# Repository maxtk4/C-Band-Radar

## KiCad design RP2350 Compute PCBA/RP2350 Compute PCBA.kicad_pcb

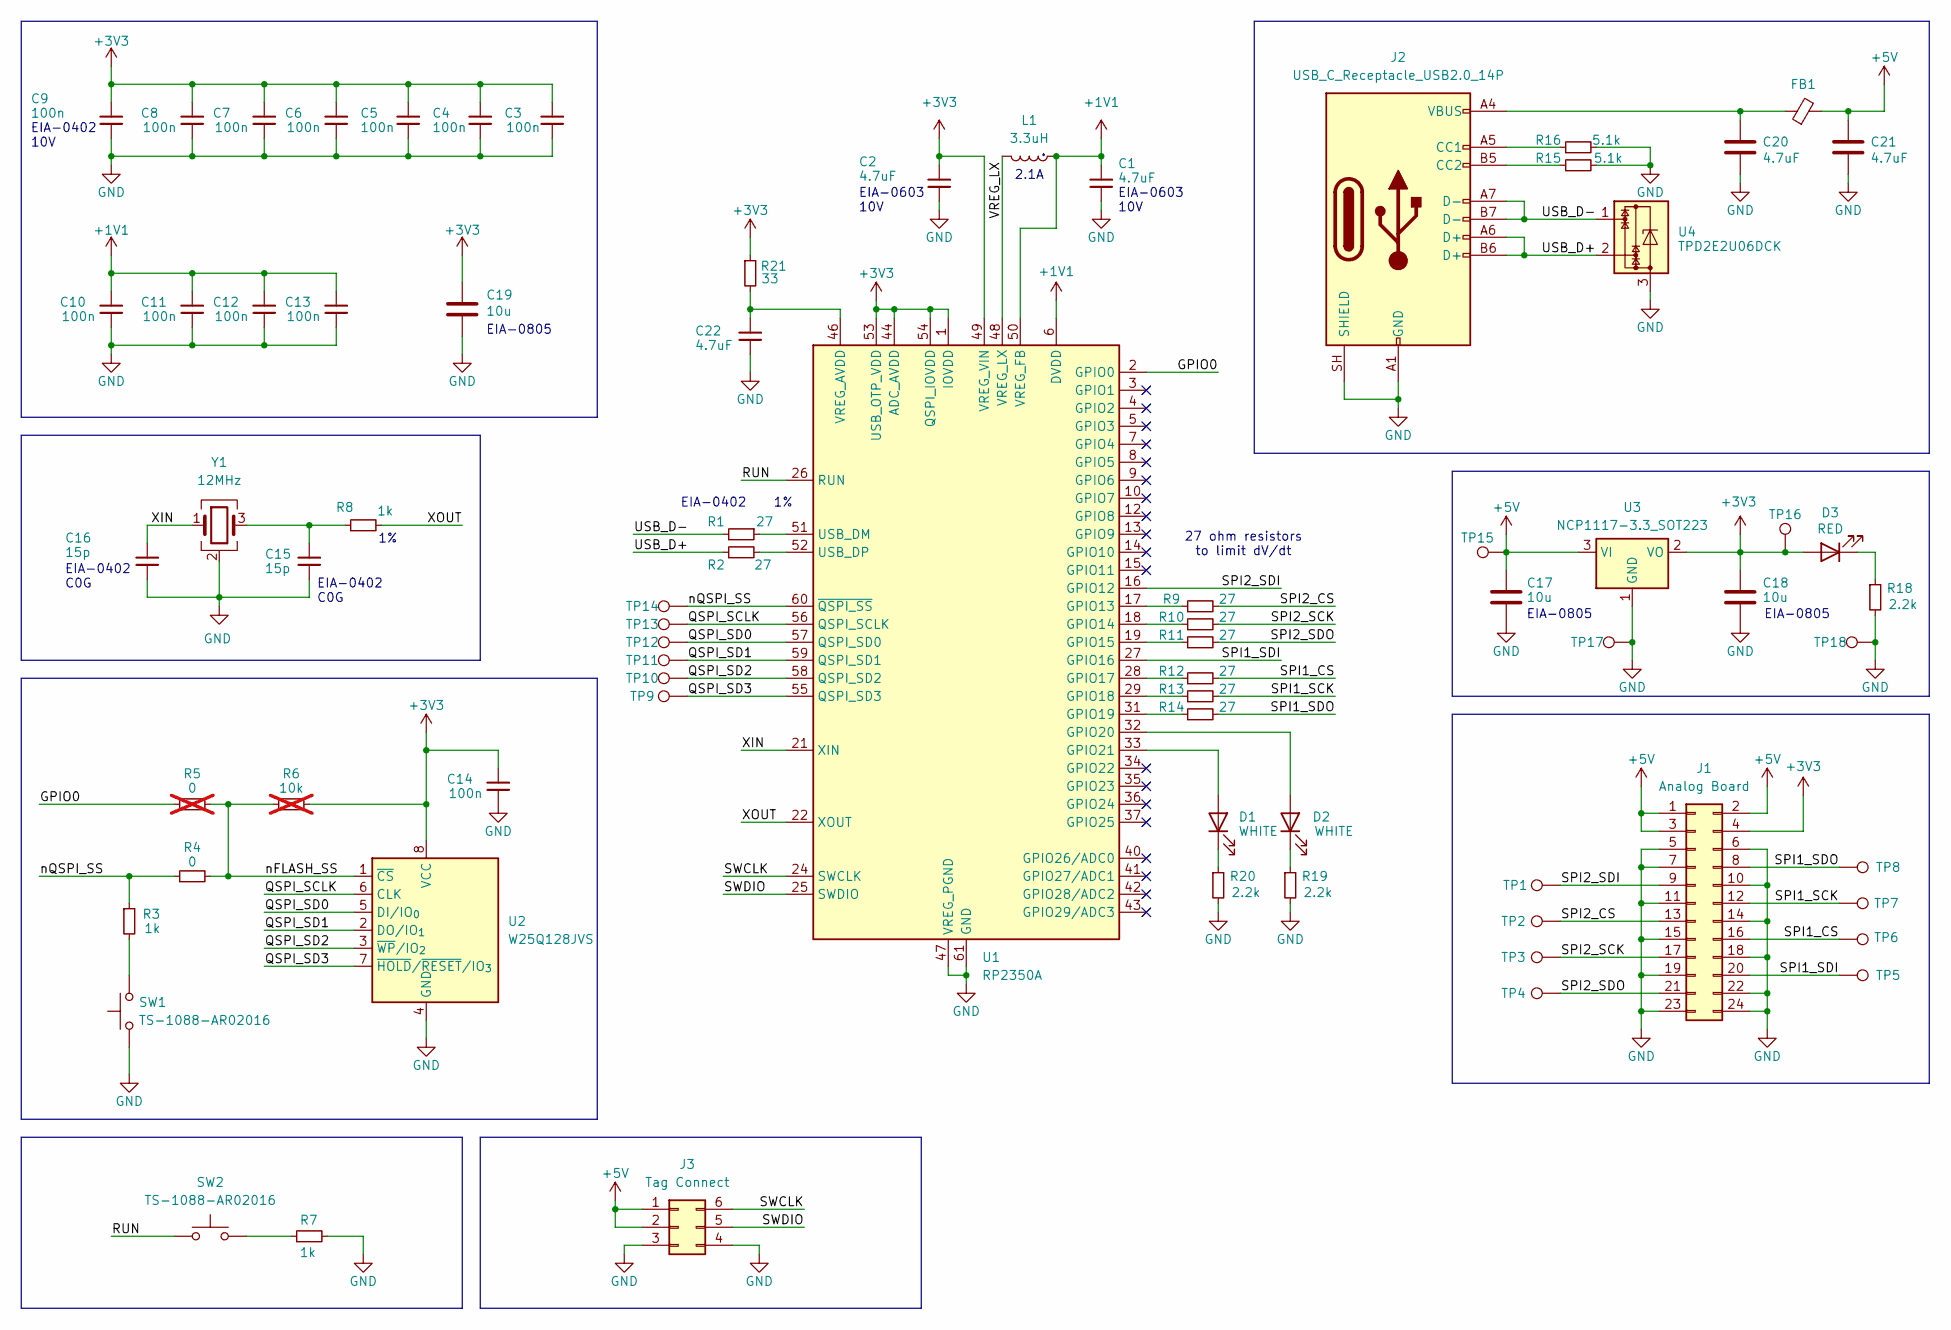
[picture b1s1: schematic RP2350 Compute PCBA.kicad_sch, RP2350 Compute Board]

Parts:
C1, C2, C22: 4.7uF; C_0402_1005Metric
C3, C4, C5, C6, C7, C8, C9, C10, C11, C12, C13, C14: 100n; C_0402_1005Metric
C15, C16: 15p; C_0402_1005Metric
C17, C18, C19: 10u; C_0805_2012Metric
C20, C21: 4.7uF; C_0603_1608Metric
D1, D2: WHITE; LED_0603_1608Metric
D3: RED; LED_0603_1608Metric
FB1: FerriteBead_Small; L_0805_2012Metric
J1: Analog Board; Molex_SlimStack_55560-0241_2x12_P0.50mm_Vertical
J2: USB_C_Receptacle_USB2.0_14P; USB_C_Receptacle_GCT_USB4110
J3: Tag Connect; Tag-Connect_TC2030-IDC-FP_2x03_P1.27mm_Vertical
L1: 3.3uH; L_0805_2012Metric
R1, R2, R9, R10, R11, R12, R13, R14: 27; R_0402_1005Metric
R3, R7, R8: 1k; R_0402_1005Metric
R4: 0; R_0603_1608Metric
R5: 0; R_0603_1608Metric; not fitted
R6: 10k; R_0603_1608Metric; not fitted
R15, R16: 5.1k; R_0402_1005Metric
R18, R19, R20: 2.2k; R_0402_1005Metric
R21: 33; R_0402_1005Metric
SW1, SW2: TS-1088-AR02016; SW_SPST_TS-1088-xR020
TP1, TP2, TP3, TP4, TP5, TP6, TP7, TP8, TP9, TP10, TP11, TP12, TP13, TP14: TestPoint; TestPoint_Pad_D1.0mm
TP15, TP16, TP17, TP18: TestPoint; TestPoint_Pad_D1.5mm
U1: RP2350A; QFN-60-1EP_7x7mm_P0.4mm_EP3.4x3.4mm
U2: W25Q128JVS; SOIC-8_5.3x5.3mm_P1.27mm
U3: NCP1117-3.3_SOT223; SOT-223-3_TabPin2
U4: TPD2E2U06DCK; SOT-323_SC-70
Y1: 12MHz; Crystal_SMD_SeikoEpson_TSX3225-4Pin_3.2x2.5mm

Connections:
+1V1: C1.1, C10.1, C11.1, C12.1, C13.1, L1.1, U1.6 (DVDD), U1.23 (DVDD), U1.39 (DVDD), U1.50 (VREG_FB)
+3V3: C2.1, C3.1, C4.1, C5.1, C6.1, C7.1, C8.1, C9.1, C14.1, C18.1, C19.1, D3.2 (A), J1.4, R6.1, R21.1, TP16.1 (1_1), U1.1 (IOVDD), U1.11 (IOVDD), U1.20 (IOVDD), U1.30 (IOVDD), U1.38 (IOVDD), U1.44 (ADC_AVDD), U1.45 (IOVDD), U1.49 (VREG_VIN), U1.53 (USB_OTP_VDD), U1.54 (QSPI_IOVDD), U2.8 (VCC), U3.2 (VO)
+5V: C17.1, C21.1, FB1.2, J1.1, J1.2, J1.3, J3.1, J3.2, TP15.1 (1_1), U3.3 (VI)
/GPIO0: R5.1, U1.2 (GPIO0)
/QSPI_SCLK: TP13.1 (1_1), U1.56 (QSPI_SCLK), U2.6 (CLK)
/QSPI_SD0: TP12.1 (1_1), U1.57 (QSPI_SD0), U2.5 (DI/IO_{0})
/QSPI_SD1: TP11.1 (1_1), U1.59 (QSPI_SD1), U2.2 (DO/IO_{1})
/QSPI_SD2: TP10.1 (1_1), U1.58 (QSPI_SD2), U2.3 (~WP/IO_{2})
/QSPI_SD3: TP9.1 (1_1), U1.55 (QSPI_SD3), U2.7 (~HOLD/~RESET/IO_{3})
/RUN: SW2.1, U1.26 (RUN)
/SPI1_CS: J1.16, R12.2, TP6.1 (1_1)
/SPI1_SCK: J1.12, R13.2, TP7.1 (1_1)
/SPI1_SDI: J1.20, TP5.1 (1_1), U1.27 (GPIO16)
/SPI1_SDO: J1.8, R14.2, TP8.1 (1_1)
/SPI2_CS: J1.13, R9.2, TP2.1 (1_1)
/SPI2_SCK: J1.17, R10.2, TP3.1 (1_1)
/SPI2_SDI: J1.9, TP1.1 (1_1), U1.16 (GPIO12)
/SPI2_SDO: J1.21, R11.2, TP4.1 (1_1)
/SWCLK: J3.6, U1.24 (SWCLK)
/SWDIO: J3.5, U1.25 (SWDIO)
/USB_D+: J2.A6 (D+), J2.B6 (D+), R2.1, U4.2
/USB_D-: J2.A7 (D-), J2.B7 (D-), R1.2, U4.1
/VREG_LX: L1.2, U1.48 (VREG_LX)
/XIN: C16.1, U1.21 (XIN), Y1.1
/XOUT: R8.2, U1.22 (XOUT)
/nFLASH_SS: R4.2, R5.2, R6.2, U2.1 (~CS)
/nQSPI_SS: R3.1, R4.1, TP14.1 (1_1), U1.60 (~QSPI_SS)
GND: C1.2, C2.2, C3.2, C4.2, C5.2, C6.2, C7.2, C8.2, C9.2, C10.2, C11.2, C12.2, C13.2, C14.2, C15.2, C16.2, C17.2, C18.2, C19.2, C20.2, C21.2, C22.2, J1.5, J1.6, J1.7, J1.10, J1.11, J1.14, J1.15, J1.18, J1.19, J1.22, J1.23, J1.24, J2.A1 (GND), J2.A12 (GND), J2.B1 (GND), J2.B12 (GND), J2.SH (SHIELD), J3.3, J3.4, R7.2, R15.2, R16.2, R18.2, R19.2, R20.2, SW1.1, TP17.1 (1_1), TP18.1 (1_1), U1.47 (VREG_PGND), U1.61 (GND), U2.4 (GND), U3.1 (GND), U4.3, Y1.2 (G), Y1.4 (G)
unnamed: C15.1, R8.1, Y1.3
unnamed: C20.1, FB1.1, J2.A4 (VBUS), J2.A9 (VBUS), J2.B4 (VBUS), J2.B9 (VBUS)
unnamed: D1.2 (A), U1.33 (GPIO21)
unnamed: D1.1 (K), R20.1
unnamed: D2.2 (A), U1.32 (GPIO20)
unnamed: D2.1 (K), R19.1
unnamed: D3.1 (K), R18.1
unnamed: J2.A5 (CC1), R16.1
unnamed: J2.B5 (CC2), R15.1
unnamed: R3.2, SW1.2
unnamed: R7.1, SW2.2
unnamed: R9.1, U1.17 (GPIO13)
unnamed: R10.1, U1.18 (GPIO14)
unnamed: R11.1, U1.19 (GPIO15)
unnamed: R12.1, U1.28 (GPIO17)
unnamed: R13.1, U1.29 (GPIO18)
unnamed: R14.1, U1.31 (GPIO19)
unnamed: R1.1, U1.51 (USB_DM)
unnamed: R2.2, U1.52 (USB_DP)
unnamed: C22.1, R21.2, U1.46 (VREG_AVDD)

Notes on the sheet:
EIA-0402 C0G
27 ohm resistors to limit dV/dt
EIA-0402 1%
EIA-0402 10V
EIA-0805
EIA-0603 10V
2.1A

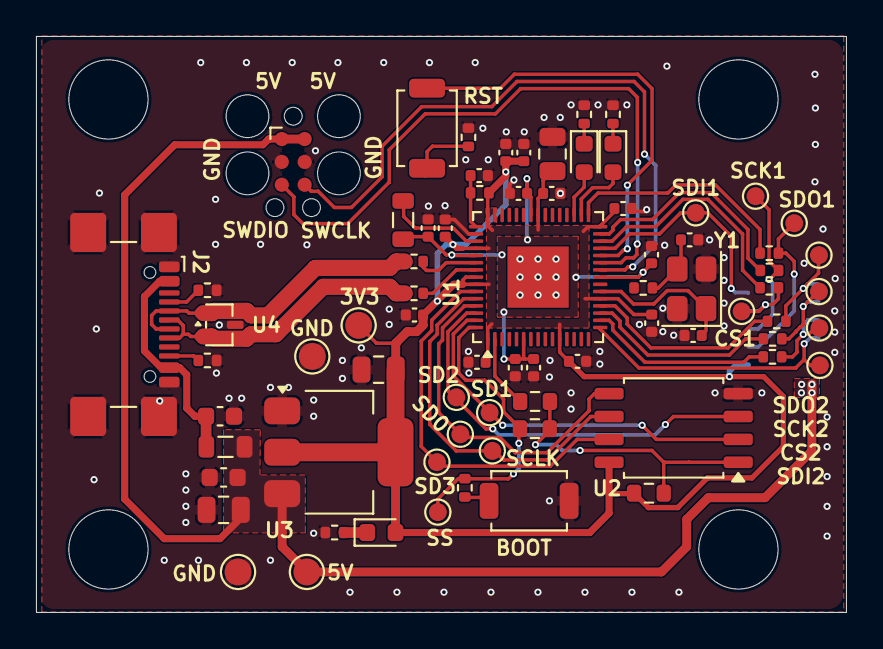
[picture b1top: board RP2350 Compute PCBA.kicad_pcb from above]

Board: 2 copper layers, 45.0 x 32.0 mm, 75 parts (1 on the bottom side), 48 nets.

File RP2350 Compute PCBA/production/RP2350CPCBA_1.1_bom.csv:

Designator,Footprint,Quantity,Value,LCSC Part #
"C1, C2, C22",0402,3,4.7uF,
"C10, C11, C12, C13, C14, C3, C4, C5, C6, C7, C8, C9",0402,12,100n,
"C15, C16",0402,2,15p,
"C17, C18, C19",0805,3,10u,
"C20, C21",0603,2,4.7uF,
"D1, D2",0603,2,WHITE,
D3,0603,1,RED,
FB1,0805,1,FerriteBead_Small,
J1,Molex_SlimStack_55560-0241_2x12_P0.50mm_Vertical,1,Analog Board,
J2,USB_C_Receptacle_GCT_USB4110,1,USB_C_Receptacle_USB2.0_14P,
J3,Tag-Connect_TC2030-IDC-FP_2x03_P1.27mm_Vertical,1,Tag Connect,
L1,0805,1,3.3uH,
"R1, R10, R11, R12, R13, R14, R2, R9",0402,8,27,
"R15, R16",0402,2,5.1k,
R17,0805,1,1M,
"R18, R19, R20",0402,3,2.2k,
R21,0402,1,33,
"R3, R7, R8",0402,3,1k,
"R4, R5",0603,2,0,
R6,0603,1,10k,
"SW1, SW2",SW_SPST_TS-1088-xR020,2,TS-1088-AR02016,
U1,QFN-60-1EP_7x7mm_P0.4mm_EP3.4x3.4mm,1,RP2350A,
U2,SOIC-8_5.3x5.3mm_P1.27mm,1,W25Q128JVS,
U3,SOT-223-3_TabPin2,1,NCP1117-3.3_SOT223,
U4,SOT-323_SC-70,1,TPD2E2U06DCK,
Y1,Crystal_SMD_SeikoEpson_TSX3225-4Pin_3.2x2.5mm,1,12MHz,
